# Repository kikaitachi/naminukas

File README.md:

# naminukas

Pneumatic walking, driving and wall climbing robot.

## Contributing

### Commit Message Guidelines

See [Conventional Commits](https://www.conventionalcommits.org/en/v1.0.0/).

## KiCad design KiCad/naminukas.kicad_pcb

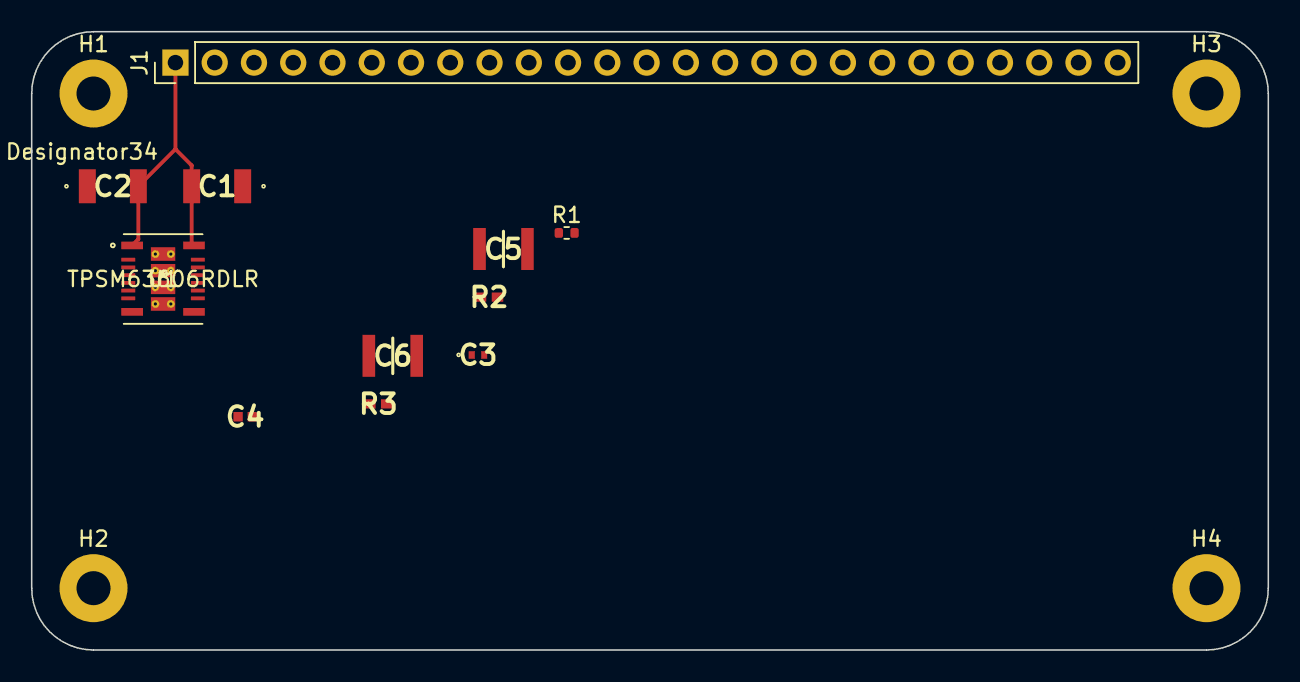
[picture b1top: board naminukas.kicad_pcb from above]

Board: 4 copper layers, 80.0 x 40.0 mm, 15 parts (0 on the bottom side), 6 nets.

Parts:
C1, C2: 10uF; C3225_Commercial
C3: 1uF; C1005_Commercial
C4: 8.2pF; CAPC1005X55N
C5, C6: 47uF; CAPC3225X270N
H1, H2, H3, H4: Mounting hole; MountingHole_2.2mm_M2_Pad
J1: Conn_01x25; PinHeader_1x25_P2.54mm_Vertical
R1: 12.1k; R_0402_1005Metric
R2: 40.2k; RESC1005X40N
R3: 10k; RESC1005X40N
U1: TPSM63606RDLR; RDL0020A-MFG

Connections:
+BATT: C1.2, C2.2, J1.1, U1.1 (VIN), U1.14 (EN_SYNC), U1.16 (VIN)
GND: C1.1, C2.1, C3.1, C5.1, C6.1, J1.2, R1.2, R3.1, U1.6 (AGND), U1.11 (AGND), U1.17 (PGND), U1.18 (PGND), U1.19 (PGND), U1.20 (PGND)
unnamed: C4.1, R2.1, R3.2, U1.10 (FB)
unnamed: R1.1, U1.12 (RT)
unnamed: U1.3 (CBOOT), U1.4 (RBOOT)
VCC5: C3.2, C4.2, C5.2, C6.2, R2.2, U1.5 (VLDOIN), U1.8 (VOUT), U1.9 (VOUT)

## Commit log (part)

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2020-03-21 Add server.js to serve files via node for testing on localhost
2020-03-21 Add BreadcrumbList and Description metadata
2020-03-21 Add missing comma
2020-03-21 Dynamically add favicon
2020-03-21 Add missing charset meta tag
2020-03-21 Replace deprecated frameborder attribute with css
2020-03-21 Don't nest block tags inside p tags
2020-03-21 Add stylesheet dynamically to minimize need to copy paste when creating new pages
2020-03-21 Add description metadata to all pages
2020-03-21 Use links without .html suffix
2020-03-21 Support paths without .html in local server to match GitHub functionality
2020-03-21 Fix selected menu item display
2020-03-21 Write motivation blog entry
2020-03-21 Add prev/next navigation to blog posts
2020-03-21 Add an image of an early prototype
2020-03-21 Add an image of the first fully functional version
2020-03-21 Add img alt attributes
2020-03-21 Add more text to blog entries
2020-03-21 Mention 2 wheel mode in home page too
2020-03-21 Fix URL in sitemap
2020-03-21 Fix breadcrumb usage
2020-03-21 regading -> regarding
2020-03-21 Add logo metadata
2020-03-22 holts -> holds
2020-03-22 Postpone blog entry about 3D printed parts to the next week
2020-03-22 Update home page video to be door climbing one
2020-03-22 waling -> walking
2020-03-22 Add picture of pneumatic rotary joint
2020-03-29 Write a blog entry about 3D printed pneumatic part
2020-04-05 Add blog entry about transforming to 2 wheel mode
2020-04-05 Add one more donation milestone
2020-04-05 Fix typos
2020-04-05 Add canonical URLs
2020-04-05 Use nav element instead for div for menu navigation
2020-04-07 Add Bing site authentication file
2020-04-07 Make only menu item clickable not 250px bellow too
2020-04-09 New blog entry about lighter wheel
2020-04-09 Link to correct scales
2020-04-09 Remove duplicate word
2020-04-15 Update meta description for home page
2020-04-15 Add robots.txt
2020-04-15 Update page titles and descriptions
2020-04-16 Add new blog entry
2020-04-16 Add more contact options
2020-04-18 Simplify menu markup
2020-04-18 Code cleanup
2020-04-24 New blog entry
2020-04-24 Fix typo
2020-04-30 Use a better video to demonstrate walk <-> drive transformation on home page
2020-04-30 Update home page with single video demonstrating all modes of operation
2020-05-01 Use consistent capitalization of robot name
2020-05-01 Add blog entries to sitemap
2020-05-02 Add vacuum pump and cups to part list
2020-05-02 Add BeagleBone Blue to part list
2020-05-02 Add Dynamixel to part list
2020-05-02 Add U2D2 to part list
2020-05-02 Add HN12-I101 to part list
2020-05-02 Add pneumatic air tubing to part list
2020-05-02 Add OpenScad files for 3D printable parts
2020-05-02 Link to 3D models from home page
2020-05-02 Link to required libraries to use .scad files
2020-05-02 Add rotart pneumatic joint to part list
2020-05-02 Add 3 way pneumatic fitting to part list
2020-05-02 Add KingMax high voltage servo to part list
2020-05-02 Add model for BeagleBone Blue holder
2020-05-02 Add 2S LiPo battery to part list
2020-05-03 Got permission to add the first ever contributor name to donate page
2020-05-04 Add bearings to part list
2020-05-04 Add o-rings to part list
2020-05-04 Add wires to part list
2020-05-10 Replace contact page with footer links
2020-05-10 Link to patreon page
2020-05-11 New blog post about 4DOF arm
2020-05-11 Add patreon link to donate page
2020-05-14 Add tool related models
2020-05-16 Remove unnecessary holes
2020-05-18 Redesign of wheel
2020-05-23 Add link to Twitter
2020-05-25 Add animated gifs to demonstrate robot capabilities
2020-05-25 Handle gif mime type
2020-05-25 Add showcase of robot capabilities to the home page
2020-06-01 Suggest being second donor
2020-06-04 Add missing word
2020-06-15 Add camera holder model
2020-06-15 Update page description
2020-06-15 Make contributor table fit on larger mobile screens without wrapping
2020-06-16 Better showcase element alignment on medium size displays
2020-06-17 Add robot image
2020-06-17 Add VideoObject structured data
2020-06-18 Add third donation without name while waiting for permission from donor to display it
2020-06-19 Add new blog entry to sitemap
2020-06-21 Update FAQ page
2020-06-25 New blog entry was added
2020-06-28 Got permission to show donor name
2020-06-28 Add model for LED holder
2020-07-03 Update sitemap
2020-07-04 Add UV LED part
2020-07-04 Mention UV LED on the main page
2020-07-10 Add USB hub holder model
2020-07-13 Update blog entry
2020-07-14 Add model for valve to servo connector
2020-07-14 Add model for valve holding plate
2020-07-20 Add a screenshot of remove control software
2020-07-20 Add simple wiring diagram
2020-07-26 Add a wish list and update font
2020-07-26 Tweak styling of donate page
2020-07-26 Few more style tweaks
2020-07-26 Load wish list items sequentially
2020-07-26 Optimize images
2020-07-26 Add magnets to parts list
2020-07-28 Experiment with outdoor tires
2020-07-29 Update wish list
2020-08-04 Update remote control program screenshot
2020-09-04 Update YouTube channel link
2020-09-10 Start creating schematics
2020-09-10 Add pneumatic parts and Dynamixels to schematics
2020-09-10 Add UV LED to schematics
2020-09-10 Add laptop and some notes to schematics
2020-09-10 Move schematics to webpage folder
2020-09-10 Move schematics to images folder
2020-09-11 Schematic should be singular
2020-09-11 Add background to schematic
2020-09-19 Should be 7 magnets instead of 4
2020-09-20 Add shuffle dancing code
2020-09-20 Add link to Python program
2020-09-24 Add images used to draw schematic
2020-09-24 Add a new contributor
2020-09-28 Add webcam and USB hub to schematic
2020-09-30 Make axle 3mm longer and extract bottom plate diameter to variable
2020-10-02 Experiment with rubber foam vacuum suction cups
2020-10-07 Remove link to Tumblr as it is not maintained
2020-10-11 Create LICENSE
2020-11-02 Add roller model
2020-11-02 Add new donations from Patreon
2020-11-03 Add link for a previous video
2020-12-02 Add new donations
2020-12-26 Add GitHub sponsorship
2020-12-26 Include GitHub Sponsor as possible source of donations
2021-01-05 Move funding configuration to .github repository
2021-01-10 Self-righting mechanism v2
2021-01-16 Add experimental track model
2021-01-16 New tail design
2021-01-17 New track design
2021-01-24 Tapered pin
2021-01-24 Flip tail teeth
2021-01-25 Back to simple tail
2021-01-27 A better wording
2021-02-13 Revert to 'industrial' rubber vacuum suction cups
2021-03-27 Experiment with flower like solar panel arrangement
2021-03-29 Different colar panel prototype
2021-03-29 Support non-square panels
2021-05-02 Remove pressure sensor from wishlist
2021-05-24 New folding solar panel design ready to 3D print
2021-06-02 Record latest donations
2021-07-01 Add roadmap page
2021-07-24 Get rid of kickstarter and make everything open source
2021-07-24 Minify PNGs
2021-07-24 Fix vertical alignment
2021-07-24 Load CSS first
2021-07-24 Re-implement wish list without JavaScript
2021-07-24 Add explicit width and height for images
2021-07-24 Include CSS directly
2021-08-06 Add model for belt tensioner
2021-08-07 Aggregate donations for 2020
2021-08-21 Add belt related parts
2021-08-21 Add Go Board pins
2021-08-21 Add a script to flash Go Board
2021-08-24 Add support for iceFUN board
2021-08-25 Specify top module for Go Board build
2021-08-25 Implement sending byte via UART
2021-08-26 Add a module for Dynamixel Sync Write packet
2021-08-26 Add top module
2021-08-26 Implement CRC16 calculation
2021-08-28 Add KiCad library for BQ25792
2021-08-28 Add KiCad library for USB-C connector
2021-08-28 Add KiCad project
2021-08-30 Generalise sync write position to writing any 4 byte address
2021-08-30 Simplify code with macro
2021-08-30 Make data length an argument
2021-08-30 Support sending 1, 2 and 4 byte length data
2021-08-30 Add parameter for clock frequency
2021-08-30 Implement toggling torque every 3s as a first hardware test
2021-08-31 Add LFE5U85
2021-09-04 Record new donations
2021-09-05 Move PCB to a separate repository
2021-09-09 Remove unused variable
2021-09-11 Fix some of lint errors reported by Verilator
2021-09-11 Default branch is 'master' not 'main'
2021-09-12 Fix all Verilator warnings
2021-09-14 Add proof of concept test bench
2021-10-16 Start blog entry about F.Port
2021-10-16 Finish F.Port blog entry
2021-10-16 Salea -> Saleae
2021-10-16 Fix link to extensions documentation
2021-12-21 Remove Go-Board support
2021-12-22 docs: add contribution guidelines to README file
2021-12-23 feat: add module for fport radio
2021-12-23 build: put all useful commands into Makefile
2021-12-26 feat: implement fport_radio module
2021-12-26 More f.port experiments
2021-12-29 feat: parametrise uart module to send inverted signal
2022-01-02 fix: add debug pin and fix f.port state machine
2022-01-03 feat: send user defined sensor value to F.Port radio
2022-01-03 feat: implement CRC calculation in uplink frame
2022-01-06 feat: POC demonstration of displaying value send from FPGA in LUA widget on radio
2022-01-08 feat(build): proof of concept displaying of 3D printed part on build page
2022-01-08 feat(build): add CSS for new part lists
2022-01-08 feat(build): add BOM file
2022-01-08 feat(build): show estimated cost of all parts to buy
2022-01-08 feat(build): move all currently used parts to BOM
2022-01-09 feat(build): add radio receiver
2022-01-09 feat(bom): add voltage regulator to BOM
2022-01-09 feat(3D printing): add holes to screw voltage regulator to power & control plate
2022-01-10 feat(3D printing): add cuts to hold FPGA board by rubber band
2022-01-10 feat(build): add iceFUN FPGA to BOM
2022-01-10 fix(build): move Dynamixel idler bearing set to currently used parts BOM
2022-01-11 feat(3D printing): add gap between radio and voltage regulator
2022-01-11 feat(build): start adding 3D printed parts to BOM
2022-01-11 feat(3D print): add valve to servo connector to the BOM
2022-01-15 feat(3D print): add valve plate to BOM
2022-01-15 feat(3D print): add servo joining plate to BOM
2022-01-30 fix: only read sensor value if sensor exists
2022-01-30 fix: set background color, show battery & mode
2022-02-03 docs: add latest donation
2022-02-08 feat(pcb): add initial schematic
2022-02-13 fix(pcb): better symbol for TPSM84A21MOJR
2022-02-13 fix(pcb): better footprint for TPS84320RUQR
2022-02-13 feat(pcb): add symbol/footprint for LFE5U-85F-6MG285C
2022-02-13 fix(pcb): ignore KiCad footprint cache
2022-02-13 feat(pcb): add SPI flash W25Q128JVPIQ
2022-02-16 feat(pcb): add passives to 3.3V power schematic
2022-03-22 chore(docs): add datasheets for LSF0204DYZPR & W25Q128JVPIQ
2022-03-22 chore(pcb): split voltage regulators to separate schematics
2022-03-23 chore(pcb): start from scratch using TPSM63606RDLR
2022-03-23 feat(pcb): add input capacitors
2022-03-23 feat(pcb): add LDO capacitor
2022-03-23 feat(pcb): add resistor for switching frequency
2022-03-23 feat(pcb): add feedback resistors
2022-03-23 feat(pcb): add output capacitors
2022-03-23 feat(pcb): add footprints
2022-03-23 feat(pcb): add mounting holes
2022-03-23 feat(pcb): add schematic for connectors
2022-03-23 feat(pcb): make layer 2 copper ground plane
2022-04-18 feat(design): define parameters for new arm
2022-04-18 feat(design): create arm segment frame
2022-04-18 feat(design): add screw holes to arm segment frame
2022-04-18 fix(design): add missin screw holes to arm segment frame
2022-04-24 feat(design): add center holes to arm segment
2022-04-25 fix(design): hole spacing
2022-04-30 feat(design): add pulley
2022-04-30 fix(design): reduce pulley thickness and increase shaft diameter
2022-04-30 feat(design): add arm joint shaft bushing
2022-04-30 feature(design): add new type of arm segment frame
2022-05-01 fix(design): add holes in new arm segment frame
2022-05-08 feat(design): add tendon guide pulleys
2022-05-22 feat(design): add holes for tensioning screws
2022-06-02 feat(design): add more holes to arm segment
2022-06-11 feat(design): add single pulley
2022-06-11 feat(design): add double pulley
2022-06-11 feat(design): add shaft connector
2022-06-12 feat(design): remove overhangs from shaft connector
2022-09-24 Create CNAME
2023-07-02 chore(docs): add donations for 2023
2023-08-04 docs: new donation
2024-07-02 docs: add fees
2025-01-11 fix: make power socket higher

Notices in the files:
parts and their libraries:
Copyright 2021 Accelerated Designs. All rights reserved.
